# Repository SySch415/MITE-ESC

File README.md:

# MITE - SCX24 Electronic Speed Controller

### MITE (Micro Inline Terrain ESC)

A from-scratch Electronic Speed Controller for SCX24 rock crawlers, built around the STM32F411. It has two parts:

- **Crawler**: receives commands over a 2.4 GHz nRF24L01+ link and drives a brushed 050 motor through a TB6612FNG H-bridge plus a steering servo. Its custom board is **MITE v1**, shown above.
- **Controller**: a handheld transmitter that reads a 2-axis joystick and sends throttle and steering to the crawler.

Both firmwares are **bare-metal C++17**: no vendor HAL and no CubeMX-generated code. They're built on a register-level HAL ([STM32-HAL-Library](https://github.com/SySch415/STM32-HAL-Library), included as a submodule) and a custom nRF24L01+ driver.

> **Status**
>
> - Crawler and controller firmware run on prototype (two Black Pill boards).
> - **MITE v1** (custom crawler PCB): layout about 90% done, antenna needs impedance matching, then going through CDR, not yet fabricated. The firmware pin map has to be updated for the new board (see [Pin maps](#pin-maps)).
> - Controller PCB: schematic captured, layout not started.

---

## Contents

- [Repository layout](#repository-layout)
- [Building and flashing](#building-and-flashing)
- [Radio link](#radio-link)
- [Crawler control behavior](#crawler-control-behavior)
- [Pin maps](#pin-maps)
- [Hardware: MITE v1 crawler board](#hardware-mite-v1-crawler-board)
- [Hardware: controller](#hardware-controller)
- [First power-up checklist (MITE v1)](#first-power-up-checklist-mite-v1)
- [Roadmap](#roadmap)
- [License](#license)

---

## Repository layout

```
.
├── controller/            # Transmitter firmware (joystick → nRF24 TX)
│   ├── main.cpp
│   └── startup.cpp        # Vector table + Reset_Handler
├── crawler/               # Receiver firmware (nRF24 RX → motor + servo)
│   ├── main.cpp
│   └── startup.cpp
├── drivers/
│   ├── include/nrf24.hpp  # nRF24L01+ driver
│   └── src/nrf24.cpp
├── hal_lib/               # Submodule: SySch415/STM32-HAL-Library (GPIO, RCC, SPI, ADC, TIM)
├── hardware/
│   ├── crawler_schematic/     # KiCad project: MITE v1 crawler board
│   ├── controller_schematic/  # KiCad project: controller
│   └── original-schematic-STM32F411CEU6_WeAct_Black_Pill_V2.0.pdf  # reference
├── docs/images/           # README images
├── linker.ld              # STM32F411CE: 512 KB flash, 128 KB SRAM
└── CMakeLists.txt         # Builds controller.elf and crawler.elf
```

---

## Building and flashing

### Requirements

- `arm-none-eabi-gcc` toolchain
- CMake ≥ 3.20
- OpenOCD and an ST-Link (V2 or clone)

### Clone

The HAL is a git submodule, so clone recursively:

```bash
git clone --recursive https://github.com/SySch415/stm32-crawler.git
# or, in an existing clone:
git submodule update --init
```

### Build

```bash
cmake -B build
cmake --build build
```

This produces `controller.elf`/`.bin` and `crawler.elf`/`.bin` in `build/`.

### Flash

With the ST-Link connected to the target's SWD pins:

```bash
cmake --build build --target flash-crawler
cmake --build build --target flash-controller
```

Each target erases, writes to `0x08000000`, verifies, and resets the MCU through OpenOCD.

---

## Radio link

The controller transmits continuously, and the crawler listens on pipe 0.

| Setting               | Value                      |
| --------------------- | -------------------------- |
| RF channel            | 76 (2.476 GHz)             |
| Address               | `E7:E7:E7:E7:E7` (5 bytes) |
| Data rate / power     | 2 Mbps, 0 dBm              |
| CRC                   | 1 byte                     |
| Auto-ack / retransmit | Disabled                   |
| Payload               | 4 bytes, fixed length      |

**Payload format** (little-endian):

| Bytes | Field                 | Range                              |
| ----- | --------------------- | ---------------------------------- |
| 0–1   | Throttle (`uint16_t`) | 0–4095 (12-bit ADC), center ≈ 2048 |
| 2–3   | Steering (`uint16_t`) | 0–4095 (12-bit ADC), center ≈ 2048 |

---

## Crawler control behavior

**Throttle → TB6612FNG channel A**

- A dead band of ±100 counts around center (2048) gives **neutral**: AIN1 = AIN2 = high and PWM = 0, which puts the bridge in **short brake**. That's what keeps a crawler from rolling back down a slope.
- Above the dead band: **forward** (AIN1 high, AIN2 low), with duty scaled to the distance from center.
- Below the dead band: **reverse** (AIN1 low, AIN2 high).
- Motor PWM: timer ARR = 15999, prescaler = 0.

**Steering → servo**

- Standard RC servo frame of about 50 Hz, with a pulse of about **1.0–2.0 ms** mapped linearly from the steering axis.
- Within the steering dead band the servo holds **center (1.5 ms)**.

**Status LEDs** (prototype firmware): throttle forward/reverse and steering left/right indicators.

---

## Pin maps

### Prototype (Black Pill), matching the current firmware

**Crawler**

| Signal                    | Pin         | Peripheral     |
| ------------------------- | ----------- | -------------- |
| nRF CE                    | PA3         | GPIO           |
| nRF CSN                   | PA4         | GPIO           |
| nRF SCK                   | PA5         | SPI1 (AF5)     |
| nRF MISO                  | PA6         | SPI1 (AF5)     |
| nRF MOSI                  | PA7         | SPI1 (AF5)     |
| Motor PWM (PWMA)          | PB6         | TIM4_CH1 (AF2) |
| AIN1                      | PB7         | GPIO           |
| AIN2                      | PB8         | GPIO           |
| Servo PWM                 | PB4         | TIM3_CH1 (AF2) |
| LED throttle up / down    | PA0 / PA1   | GPIO           |
| LED steering left / right | PA11 / PA12 | GPIO           |

**Controller**

| Signal                | Pin             | Peripheral |
| --------------------- | --------------- | ---------- |
| Joystick Y (throttle) | PA0             | ADC1_IN0   |
| Joystick X (steering) | PA1             | ADC1_IN1   |
| nRF CE / CSN          | PA3 / PA4       | GPIO       |
| nRF SCK / MISO / MOSI | PA5 / PA6 / PA7 | SPI1 (AF5) |

### MITE v1 board (as routed, pending firmware update)

> Several pins moved during PCB layout. **The crawler firmware has to be updated before it runs on MITE v1.**

| Signal           | Pin           | Peripheral        | Changed? |
| ---------------- | ------------- | ----------------- | -------- |
| nRF CE           | PA3           | GPIO              | ✱        |
| nRF CSN          | PA4           | GPIO              | ✱        |
| nRF SCK          | PA5           | SPI1_SCK          |          |
| nRF MISO         | PA6           | SPI1_MISO         | ✱        |
| nRF MOSI         | PA7           | SPI1_MOSI         | ✱        |
| nRF IRQ          | not connected | (polled over SPI) |          |
| Motor PWM (PWMA) | PB4           | TIM3_CH1          | ✱        |
| AIN1             | PB6           | GPIO              | ✱        |
| AIN2             | PB5           | GPIO              | ✱        |
| Servo PWM        | PB7           | TIM4_CH2          | ✱        |
| Status LED       | PC13          | GPIO (active low) | ✱        |
| SWDIO / SWCLK    | PA13 / PA14   | SWD               |          |

---

## Hardware: MITE v1 crawler board

A 40 × 50 mm, 4-layer board that replaces the prototype's Black Pill, nRF module, H-bridge breakout and regulators. The KiCad project is in [`hardware/crawler_schematic/`](hardware/crawler_schematic).

### Main parts

| Block                       | Part                                             | Notes                                                                                  |
| --------------------------- | ------------------------------------------------ | -------------------------------------------------------------------------------------- |
| MCU                         | STM32F411CEU6 (UFQFPN48)                         | 25 MHz HSE crystal, BOOT0 and reset buttons                                            |
| Radio                       | nRF24L01+ (bare QFN-20)                          | 16 MHz crystal, Johanson 2450AT43F0100 chip antenna, Nordic reference matching network |
| Motor driver                | TB6612FNG (SSOP-24)                              | Channel A only; VM from battery                                                        |
| Reverse polarity protection | AO4407A P-channel MOSFET                         | High-side, gate to GND through 10 kΩ                                                   |
| Servo rail                  | RY8336 synchronous buck → 5 V                    | 4.7 µH molded inductor                                                                 |
| Logic / RF rail             | RY8336 synchronous buck → 3.3 V                  | 4.7 µH molded inductor                                                                 |
| Motor bulk capacitor        | 47 µF aluminum electrolytic                      | At the H-bridge VM pins                                                                |
| Battery                     | 2S LiPo (7.4 V nominal, 8.4 V full)              | JST-PH                                                                                 |
| Connectors                  | JST-PH battery, JST-PH motor, 1×3 servo, 1×4 SWD |                                                                                        |

### Power architecture

```mermaid
flowchart LR
    BAT[2S LiPo] --> FET[AO4407A<br/>reverse polarity]
    FET --> BULK[47 µF bulk cap<br/>star point]
    BULK --> HB[TB6612FNG VM] --> MOT[050 motor]
    BULK --> B5[RY8336 → 5 V] --> SERVO[Steering servo]
    BULK --> B3[RY8336 → 3.3 V]
    B3 --> MCU[STM32F411]
    B3 --> RF[nRF24L01+]
```

**Why it's arranged this way:**

- **The servo and the logic run on separate rails.** On the prototype, servo current spikes and radio TX bursts browned out the shared 3.3 V supply. The servo now has its own 5 V buck, and the 3.3 V buck runs straight from the battery.
- **The STM32 and nRF share one 3.3 V rail**, so neither chip can be back-powered through the SPI pins during power-up or power-down.
- **The battery supply splits at the bulk capacitor** (star point), so motor switching current doesn't share copper with the buck inputs.

### Stackup and layout rules

JLCPCB **JLC04161H-3313**, 1.6 mm, impedance controlled.

| Layer       | Use                                |
| ----------- | ---------------------------------- |
| L1 (F.Cu)   | Components, signals, motor current |
| L2 (In1.Cu) | Solid GND plane, no routing        |
| L3 (In2.Cu) | 3.3 V pour                         |
| L4 (B.Cu)   | Signals                            |

| Item                                 | Value                                  |
| ------------------------------------ | -------------------------------------- |
| Default track / clearance            | 0.2 mm / 0.2 mm                        |
| Motor nets (BAT_IN, +BATT, AO1, AO2) | 2.0 mm (sized for ~5 A stall)          |
| Power nets (+3.3V, +5V)              | 0.5 mm, necked down at fine-pitch pins |
| RF feed (50 Ω, grounded coplanar)    | 0.40 mm width, 0.25 mm gap             |
| Vias                                 | 0.6 mm pad / 0.3 mm drill              |
| Copper to board edge                 | 0.5 mm                                 |

### RF notes

- The antenna has a copper keepout on all four layers. Only the feed trace enters it, on F.Cu.
- Following Nordic's product specification, the nRF24L01+ **exposed die pad is left unconnected**. Ground goes through the VSS pins, each with its own via.
- Do a range test against a known-good nRF24 module before final assembly.

### Fabrication and assembly

- **Fab:** JLCPCB, 4 layers, 1.6 mm, **JLC04161H-3313 with impedance control**, with a top-side stencil.
- **Assembly:** in-house. Solder paste and stencil, hot-plate reflow, **top side only**. Headers are hand-soldered afterward. QFN bridges are reworked with hot air.
- The [Interactive HTML BOM](https://github.com/openscopeproject/InteractiveHtmlBom) KiCad plugin is used as the placement map.

### SWD header (J3)

| Pin | Signal       |
| --- | ------------ |
| 1   | +3.3 V       |
| 2   | SWDIO (PA13) |
| 3   | SWCLK (PA14) |
| 4   | GND          |

---

## Hardware: controller

Currently a prototype-level build. The KiCad schematic is in [`hardware/controller_schematic/`](hardware/controller_schematic), and the PCB isn't laid out yet.

| Part                           | Notes                         |
| ------------------------------ | ----------------------------- |
| DFRobot Black Pill (STM32F411) | MCU board                     |
| nRF24L01+ module               | SPI1                          |
| 2-axis analog joystick         | Throttle (Y) and steering (X) |
| 18650 Li-ion cell              | Power                         |
| MT3608 boost module            | 5 V for the Black Pill        |

---

## First power-up checklist (MITE v1)

1. Inspect under magnification: QFN bridges, and the orientation of the electrolytic cap, MOSFET and LEDs.
2. Power it from a **current-limited bench supply** (about 7.4 V, 200 mA limit) before connecting a LiPo.
3. Measure the rails: **3.3 V** and **5 V**.
4. Measure STM32 **VCAP_1 ≈ 1.2 V**, which confirms the internal regulator is running.
5. Connect the ST-Link and check that the MCU is detected (`openocd -f interface/stlink.cfg -f target/stm32f4x.cfg`).
6. Bring up the subsystems one at a time: radio, then servo, then motor (wheels off the ground).

---

## Roadmap

- [ ] Impedance match the antenna (add pi network??)
- [ ] Finish MITE v1 routing and DRC, then fabricate
- [ ] **Failsafe:** stop the motor and center the steering if no packet arrives within a timeout
- [ ] Range test of the chip antenna vs. an nRF24 module
- [ ] Controller PCB layout
- [ ] Battery voltage monitoring and low-voltage cutoff

---

## License

**Firmware** (`controller/`, `crawler/`, `drivers/`): [MIT](LICENSE) © 2026 Simon Schmidt  
**Hardware design files** (`hardware/`): [CERN-OHL-P v2](hardware/LICENSE) © 2026 Simon Schmidt

The Kovali name and logo are trademarks of Kovali, a California limited liability company. All rights reserved.

The ARCS name and logo belong to Avionics, Robotics, and Control Systems, a nonprofit corporation and IRS-recognized 501(c)(3) public charity, and are used with permission.

If you build, modify, or distribute this board, please remove both logos from the silkscreen.
The logo footprints are excluded from the CERN-OHL license.

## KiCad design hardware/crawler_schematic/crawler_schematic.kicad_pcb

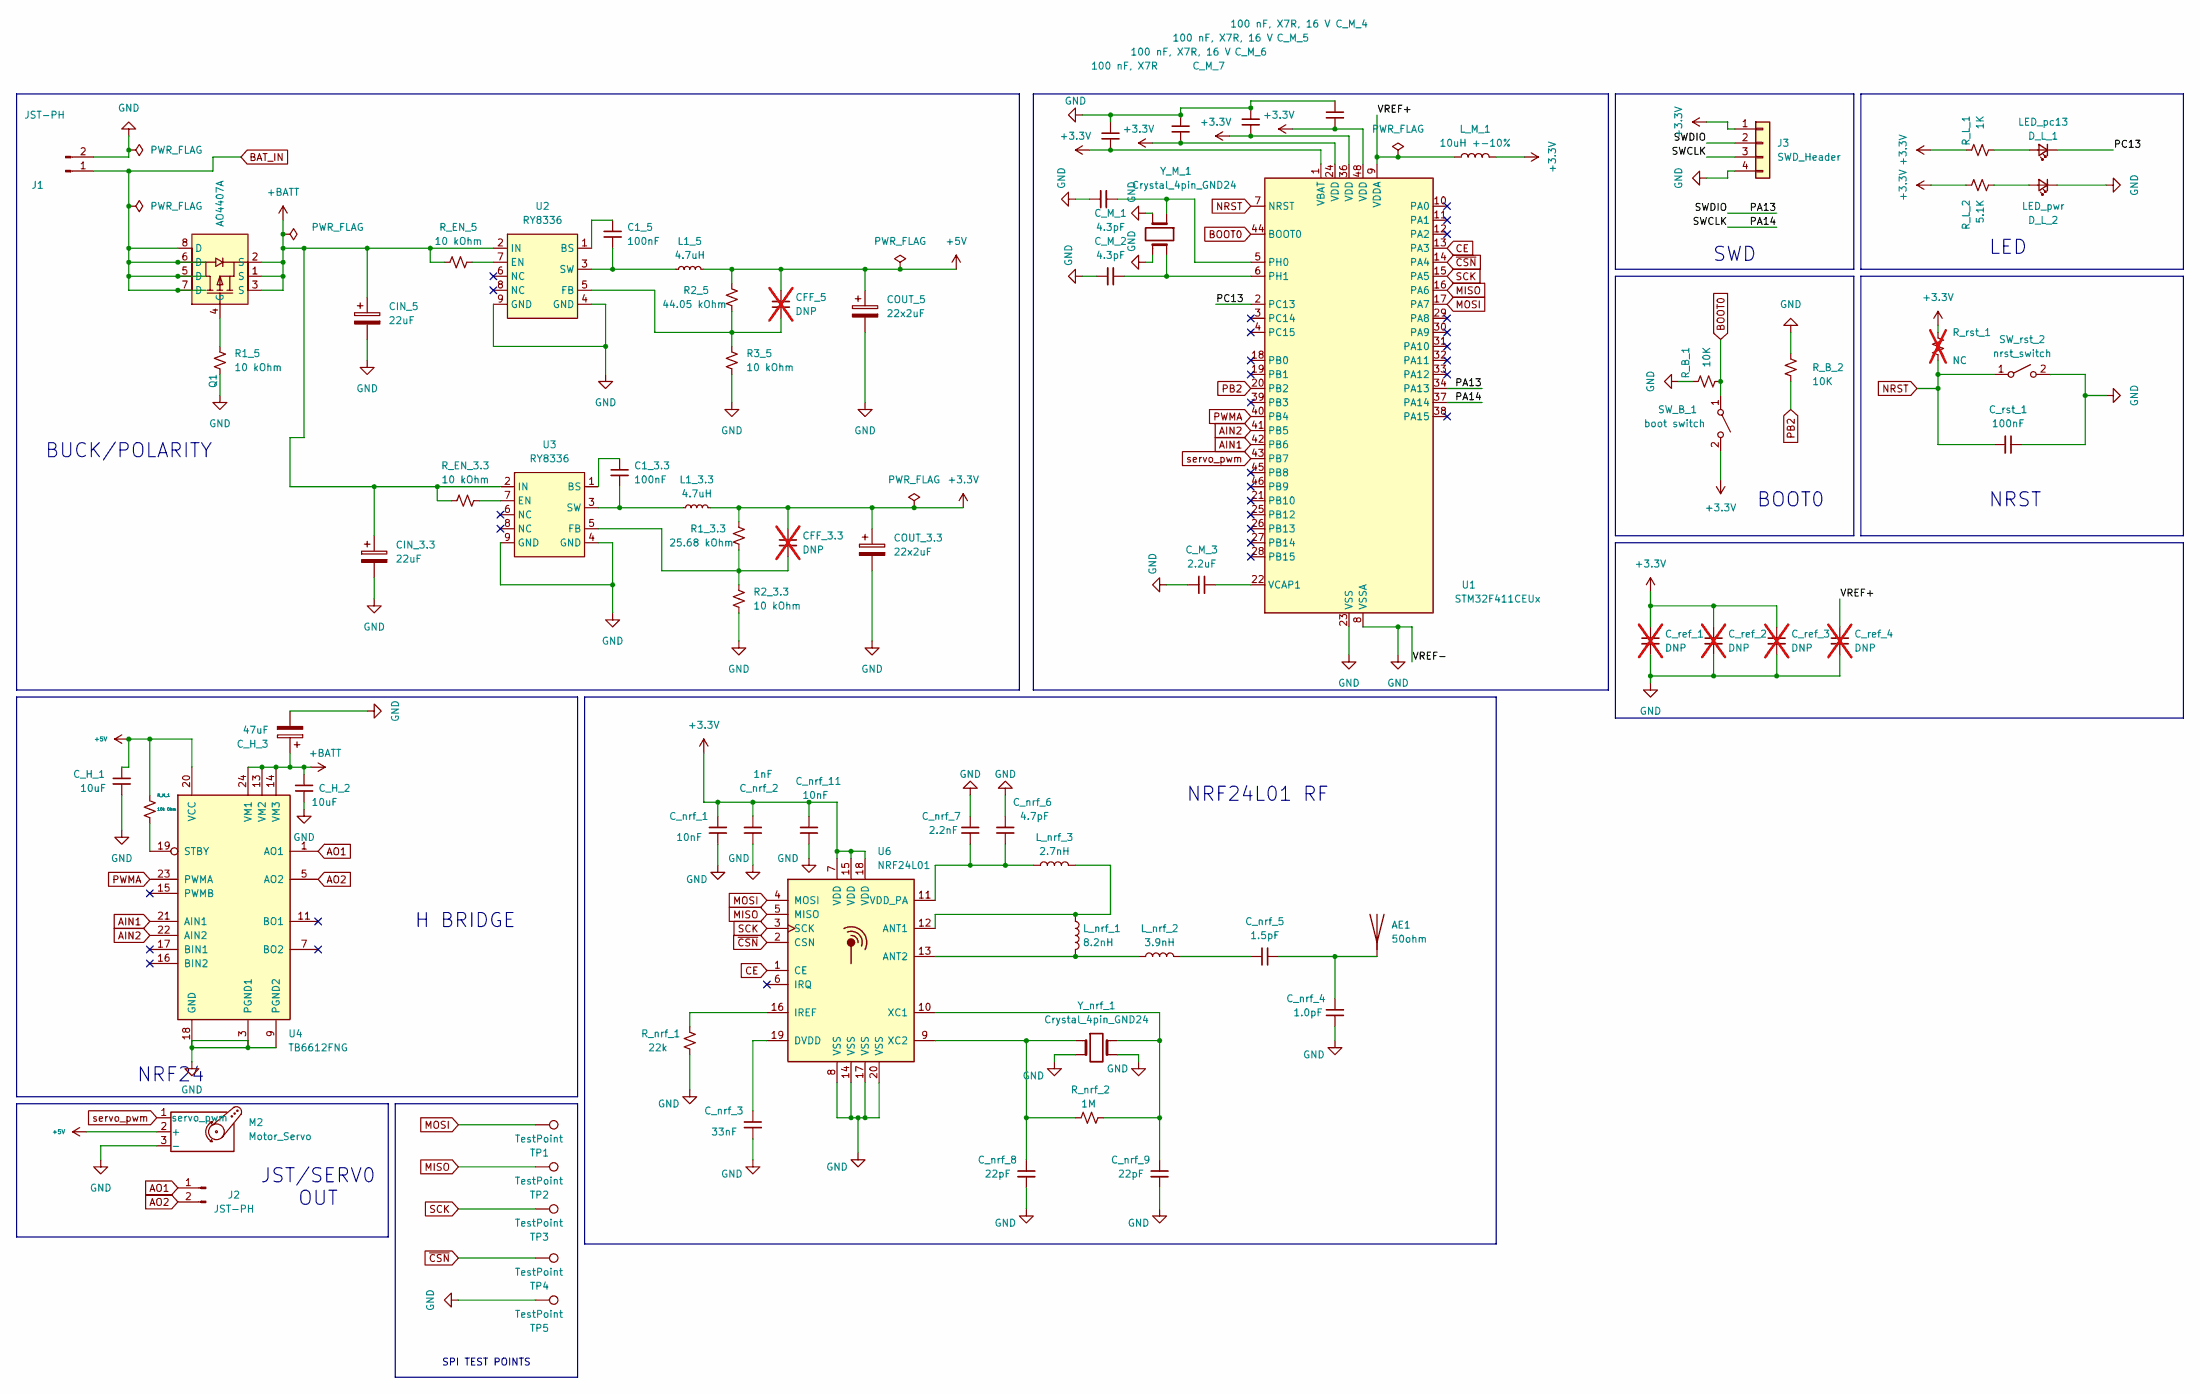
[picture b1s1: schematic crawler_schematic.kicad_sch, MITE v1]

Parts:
AE1: 50ohm; Johanson_2450AT43F0100; MPN 2450AT43F0100001E
C1_3.3, C1_5: 100nF; C_0603_1608Metric; MPN GRM188R71H104KA93D
CFF_3.3, CFF_5: DNP; C_0603_1608Metric; not fitted
CIN_3.3, CIN_5: 22uF; C_0603_1608Metric; MPN GRM188R61E106MA73D
COUT_3.3, COUT_5: 22x2uF; C_0603_1608Metric; MPN GRM188R61A226ME15D
C_H_1: 10uF; C_0603_1608Metric; MPN GRM188R61A106KE69D
C_H_2: 10uF; C_0603_1608Metric; MPN GRM188R61E106MA73D
C_H_3: 47uF; CP_Elec_6.3x5.4; MPN EEE-HA1E470WP
C_M_1, C_M_2: 4.3pF; C_0603_1608Metric; MPN GRM1885C1H120JA01D
C_M_3: 2.2uF; C_0603_1608Metric; MPN GRM188R61A475KE15D
C_M_4, C_M_5, C_M_6: 100 nF, X7R, 16 V; C_0402_1005Metric; MPN GRM155R71C104KA88D
C_M_7: 100 nF, X7R; C_0402_1005Metric; MPN GRM155R71C104KA88D
C_nrf_1, C_nrf_11: 10nF; C_0402_1005Metric; MPN GRM155R71H103KA88D
C_nrf_2: 1nF; C_0402_1005Metric; MPN GRM155R71H102KA01D
C_nrf_3: 33nF; C_0402_1005Metric; MPN GRM155R71C333KA01D
C_nrf_4: 1.0pF; C_0402_1005Metric; MPN GRM1555C1H1R0CA01D
C_nrf_5: 1.5pF; C_0402_1005Metric; MPN GRM1555C1H1R5CA01D
C_nrf_6: 4.7pF; C_0402_1005Metric; MPN GRM1555C1H4R7CA01D
C_nrf_7: 2.2nF; C_0402_1005Metric; MPN GRM155R71H222KA01D
C_nrf_8, C_nrf_9: 22pF; C_0402_1005Metric; MPN GRM1555C1H220JA01D
C_ref_1, C_ref_2, C_ref_3, C_ref_4: DNP; C_0603_1608Metric; not fitted
C_rst_1: 100nF; C_0603_1608Metric; MPN GRM188R71H104KA93D
D_L_1: LED_pc13; LED_0805_2012Metric; MPN LTST-C171TBKT
D_L_2: LED_pwr; LED_0805_2012Metric; MPN LTST-C171KRKT
J1, J2: JST-PH; JST_PH_B2B-PH-K_1x02_P2.00mm_Vertical; MPN B2B-PH-K-S(LF)(SN)
J3: SWD_Header; PinHeader_1x04_P2.54mm_Vertical
L1_3.3, L1_5: 4.7uH; IND-SMD_L3.0-W3.0_FTC303020D; MPN FTC303018D4R7MBCA; LCSC Part C5832388
L_M_1: 10uH +-10%; L_0603_1608Metric; MPN LQM18DN100M70L
L_nrf_1: 8.2nH; L_0402_1005Metric; MPN LQG15HS8N2J02D
L_nrf_2: 3.9nH; L_0402_1005Metric; MPN LQG15HS3N9S02D
L_nrf_3: 2.7nH; L_0402_1005Metric; MPN LQG15HS2N7S02D
M2: Motor_Servo; PinHeader_1x03_P2.54mm_Vertical
Q1: AO4407A; SOIC-8_L4.9-W3.9-P1.27-LS6.0-BL; MPN AO4407A; LCSC Part C16072
R1_3.3: 25.68 kOhm; R_0603_1608Metric; MPN RC0603FR-0725K5L
R1_5, R2_3.3, R3_5: 10 kOhm; R_0603_1608Metric; MPN RC0603FR-0710KL
R2_5: 44.05 kOhm; R_0603_1608Metric; MPN RC0603FR-0744K2L
R_B_1, R_B_2: 10K; R_0603_1608Metric; MPN RC0603FR-0710KL
R_EN_3.3, R_EN_5: 10 kOhm; R_0603_1608Metric; MPN RC0603FR-0710KL
R_H_1: 10k Ohm; R_0603_1608Metric; MPN RC0603FR-0710KL
R_L_1: 1K; R_0603_1608Metric; MPN RC0603FR-071KL
R_L_2: 5.1K; R_0603_1608Metric; MPN RC0603FR-075K1L
R_nrf_1: 22k; R_0603_1608Metric; MPN RC0603FR-0722KL
R_nrf_2: 1M; R_0603_1608Metric; MPN RC0603FR-071ML
R_rst_1: NC; R_0603_1608Metric; not fitted
SW_B_1: boot switch; SW_Push_1P1T_NO_CK_KMR2; MPN KMR211NG LFS
SW_rst_2: nrst_switch; SW_Push_1P1T_NO_CK_KMR2; MPN KMR211NG LFS
TP1, TP2, TP3, TP4, TP5: TestPoint; TestPoint_Pad_D1.5mm
U1: STM32F411CEUx; QFN-48-1EP_7x7mm_P0.5mm_EP5.6x5.6mm; MPN STM32F411CEU6
U2, U3: RY8336; ESOP-8_L4.9-W3.9-P1.27-LS6.0-BL-EP-1; MPN RY8336; LCSC Part C370879
U4: TB6612FNG; SSOP-24_5.3x8.2mm_P0.65mm; MPN TB6612FNG,C,8,EL; LCSC Part C141517
U6: NRF24L01; QFN-20-1EP_4x4mm_P0.5mm_EP2.5x2.5mm; MPN NRF24L01P-R
Y_M_1: Crystal_4pin_GND24; Crystal_SMD_3225-4Pin_3.2x2.5mm; MPN ABM8N-25.0000MHZ-10-D2Y-T3
Y_nrf_1: Crystal_4pin_GND24; Crystal_SMD_3225-4Pin_3.2x2.5mm; MPN ABM8AIG-16.000MHZ-12-2Z-T3

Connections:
+3.3V: CFF_3.3.1, COUT_3.3.1, C_M_4.2, C_M_5.2, C_M_6.2, C_M_7.2, C_nrf_1.1, C_nrf_2.1, C_nrf_11.1, C_ref_1.1, C_ref_2.1, C_ref_3.1, J3.1, L1_3.3.2, L_M_1.2, R1_3.3.2, R_L_1.2, R_L_2.2, R_rst_1.1, SW_B_1.2 (B), U1.1 (VBAT), U1.24 (VDD), U1.36 (VDD), U1.48 (VDD), U6.7 (VDD), U6.15 (VDD), U6.18 (VDD)
+5V: CFF_5.1, COUT_5.1, C_H_1.1, L1_5.2, M2.2 (+), R2_5.2, R_H_1.1, U4.20 (VCC)
+BATT: CIN_3.3.1, CIN_5.1, C_H_2.1, C_H_3.1, Q1.1 (S), Q1.2 (S), Q1.3 (S), R_EN_3.3.2, R_EN_5.2, U2.2 (IN), U3.2 (IN), U4.13 (VM2), U4.14 (VM3), U4.24 (VM1)
/PA13: J3.2, U1.34 (PA13)
/PA14: J3.3, U1.37 (PA14)
/PC13: D_L_1.1 (K), U1.2 (PC13)
/VREF+: C_ref_4.1, L_M_1.1, U1.9 (VDDA)
AIN1: U1.42 (PB6), U4.21 (AIN1)
AIN2: U1.41 (PB5), U4.22 (AIN2)
AO1: J2.1, U4.1 (AO1), U4.2 (AO1)
AO2: J2.2, U4.5 (AO2), U4.6 (AO2)
BAT_IN: J1.1, Q1.5 (D), Q1.6 (D), Q1.7 (D), Q1.8 (D)
BOOT0: R_B_1.1, SW_B_1.1 (A), U1.44 (BOOT0)
CE: U1.13 (PA3), U6.1 (CE)
GND: CIN_3.3.2, CIN_5.2, COUT_3.3.2, COUT_5.2, C_H_1.2, C_H_2.2, C_H_3.2, C_M_1.1, C_M_2.1, C_M_3.1, C_M_4.1, C_M_5.1, C_M_6.1, C_M_7.1, C_nrf_1.2, C_nrf_2.2, C_nrf_3.2, C_nrf_4.2, C_nrf_6.1, C_nrf_7.1, C_nrf_8.2, C_nrf_9.2, C_nrf_11.2, C_ref_1.2, C_ref_2.2, C_ref_3.2, C_ref_4.2, C_rst_1.2, D_L_2.1 (K), J1.2, J3.4, M2.3 (-), R1_5.1, R2_3.3.1, R3_5.1, R_B_1.2, R_B_2.1, R_nrf_1.2, SW_rst_2.2 (B), TP5.1 (1_1), U1.8 (VSSA), U1.23 (VSS), U1.35 (VSS), U1.47 (VSS), U1.49 (VSS), U2.4 (GND), U2.9 (GND), U3.4 (GND), U3.9 (GND), U4.3 (PGND1), U4.4 (PGND1), U4.9 (PGND2), U4.10 (PGND2), U4.18 (GND), U6.8 (VSS), U6.14 (VSS), U6.17 (VSS), U6.20 (VSS), Y_M_1.2 (GND), Y_M_1.4 (GND), Y_nrf_1.2 (GND), Y_nrf_1.4 (GND)
MISO: TP2.1 (1_1), U1.16 (PA6), U6.5 (MISO)
MOSI: TP1.1 (1_1), U1.17 (PA7), U6.4 (MOSI)
NRST: C_rst_1.1, R_rst_1.2, SW_rst_2.1 (A), U1.7 (NRST)
unnamed: AE1.1 (A_1), C_nrf_4.1, C_nrf_5.2
unnamed: C_nrf_5.1, L_nrf_2.2
unnamed: D_L_1.2 (A), R_L_1.1
unnamed: D_L_2.2 (A), R_L_2.1
unnamed: Q1.4 (G), R1_5.2
unnamed: C_M_1.2, U1.5 (PH0), Y_M_1.1
unnamed: C_M_2.2, U1.6 (PH1), Y_M_1.3
unnamed: C_M_3.2, U1.22 (VCAP1)
unnamed: C1_5.1, U2.1 (BS)
unnamed: R_EN_5.1, U2.7 (EN)
unnamed: CFF_5.2, R2_5.1, R3_5.2, U2.5 (FB)
unnamed: C1_5.2, L1_5.1, U2.3 (SW)
unnamed: C1_3.3.1, U3.1 (BS)
unnamed: R_EN_3.3.1, U3.7 (EN)
unnamed: CFF_3.3.2, R1_3.3.1, R2_3.3.2, U3.5 (FB)
unnamed: C1_3.3.2, L1_3.3.1, U3.3 (SW)
unnamed: R_H_1.2, U4.19 (STBY)
unnamed: L_nrf_1.1, L_nrf_3.2, U6.12 (ANT1)
unnamed: L_nrf_1.2, L_nrf_2.1, U6.13 (ANT2)
unnamed: C_nrf_3.1, U6.19 (DVDD)
unnamed: R_nrf_1.1, U6.16 (IREF)
unnamed: C_nrf_6.2, C_nrf_7.2, L_nrf_3.1, U6.11 (VDD_PA)
unnamed: C_nrf_9.1, R_nrf_2.1, U6.10 (XC1), Y_nrf_1.3
unnamed: C_nrf_8.1, R_nrf_2.2, U6.9 (XC2), Y_nrf_1.1
PB2: R_B_2.2, U1.20 (PB2)
PWMA: U1.40 (PB4), U4.23 (PWMA)
SCK: TP3.1 (1_1), U1.15 (PA5), U6.3 (SCK)
servo_pwm: M2.1 (servo_pwm), U1.43 (PB7)
~CSN: TP4.1 (1_1), U1.14 (PA4), U6.2 (CSN)

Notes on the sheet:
LED
SPI TEST POINTS
NRF24L01 RF
BUCK/POLARITY
BOOT0
JST/SERV0 OUT
H BRIDGE
NRST
SWD
NRF24

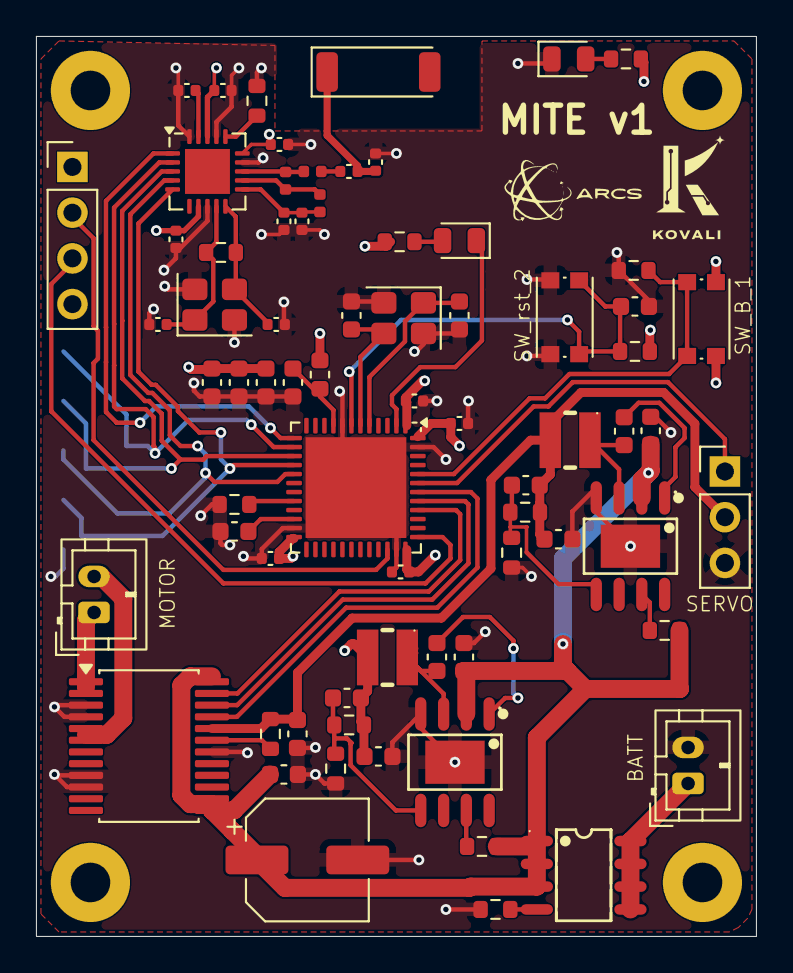
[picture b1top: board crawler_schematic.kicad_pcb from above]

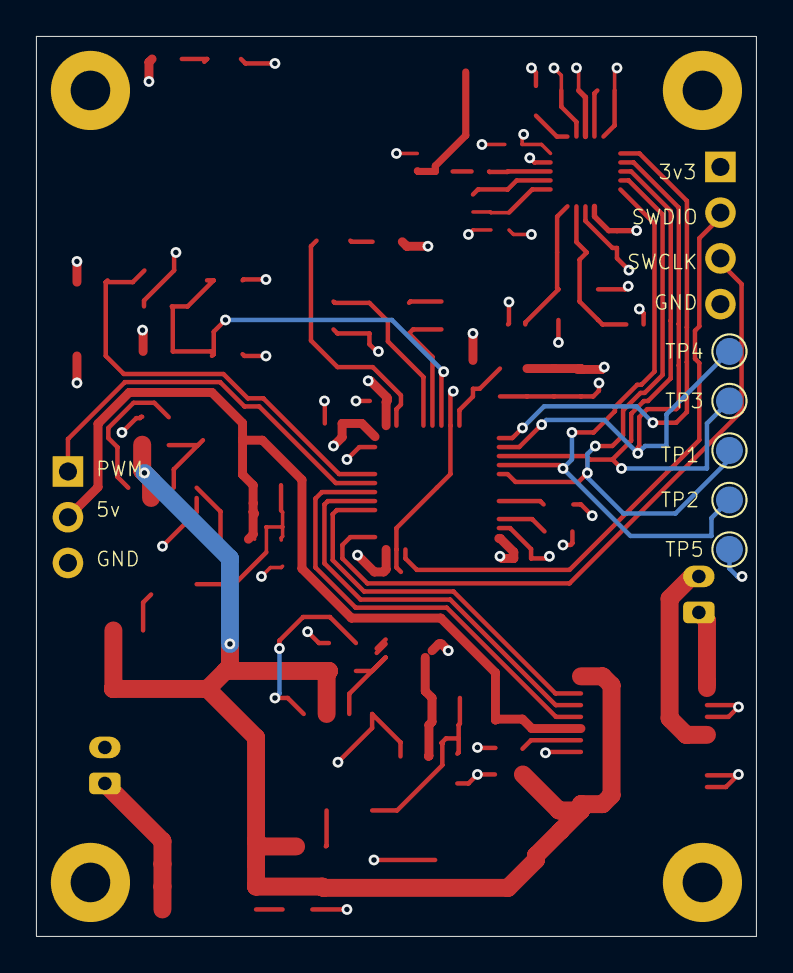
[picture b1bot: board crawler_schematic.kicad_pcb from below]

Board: 4 copper layers, 40.0 x 50.0 mm, 76 parts (5 on the bottom side), 47 nets.
